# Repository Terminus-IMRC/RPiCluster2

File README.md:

# RPiCluster2

Yet another Raspberry Pi cluster, which can **chain up to 1+32 Raspberry
Pi's**!!!

The Pi on the Motherboard (master) is always turned on, while the other Pi's
(slaves) are turned on/off by the master via I2C.  The master can choose a slave
to communicate with over UART.

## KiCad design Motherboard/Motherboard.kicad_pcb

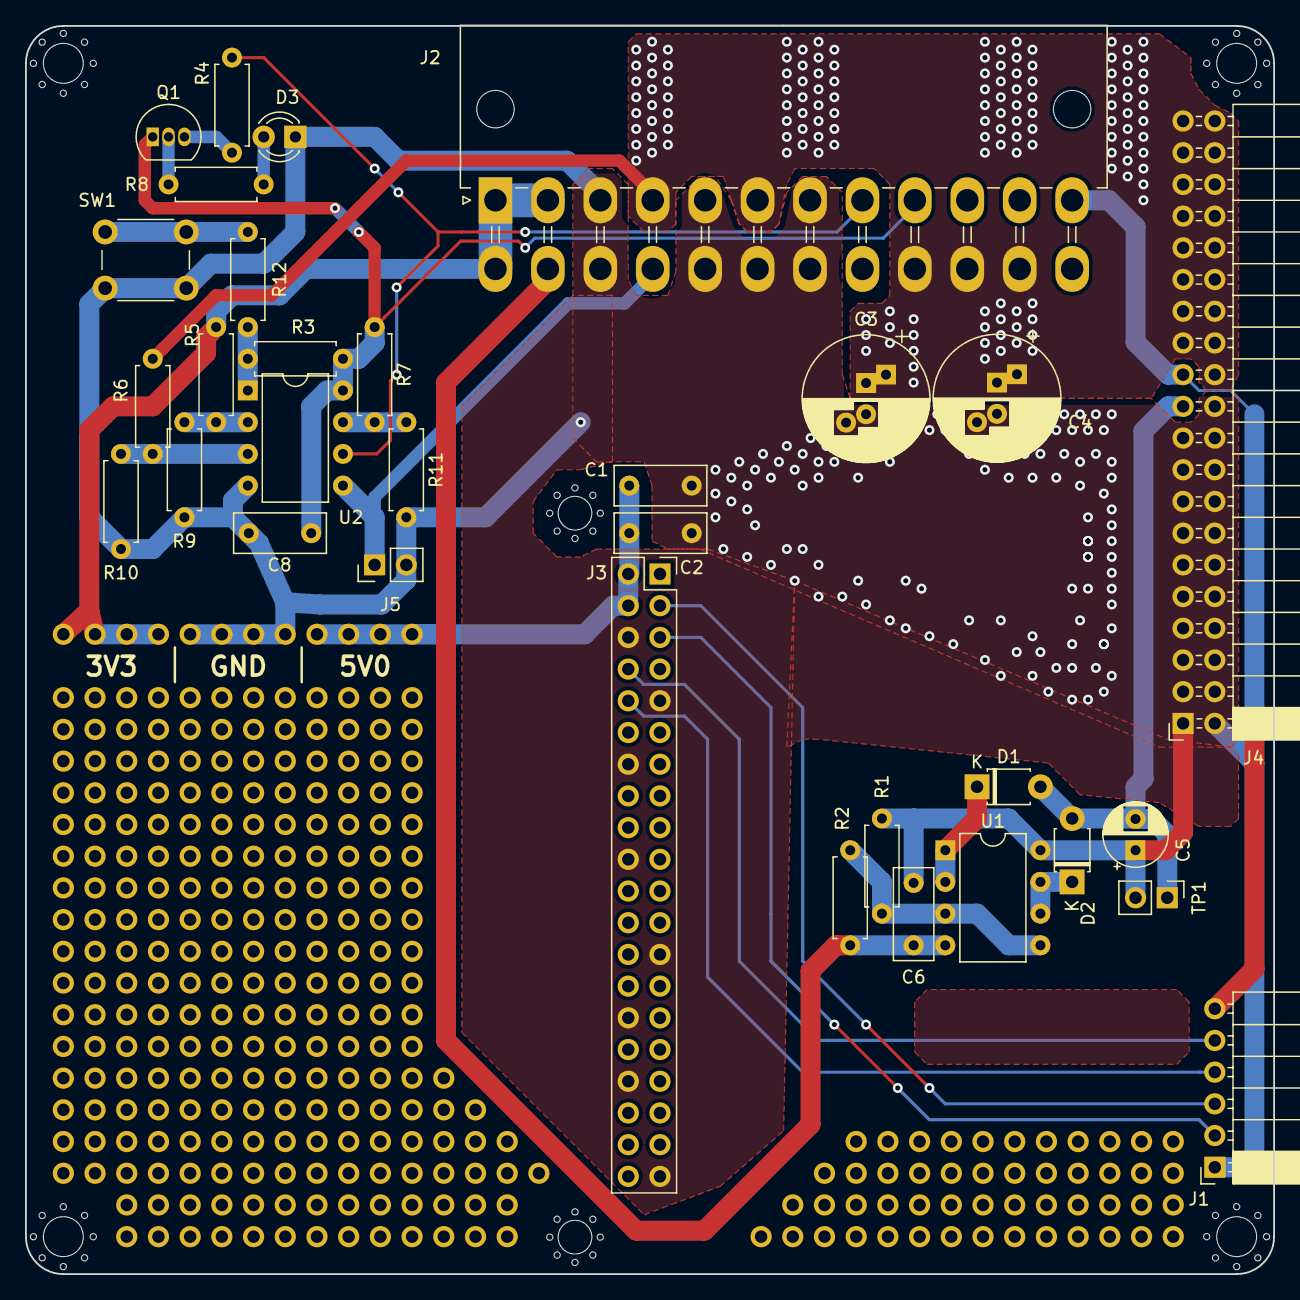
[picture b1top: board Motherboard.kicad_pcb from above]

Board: 2 copper layers, 100.0 x 100.0 mm, 32 parts (0 on the bottom side), 23 nets.

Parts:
C1, C2, C6, C8: 10u; C_Rect_L7.2mm_W3.0mm_P5.00mm_FKS2_FKP2_MKS2_MKP2
C3, C4: 470u; CP_Radial_D10.0mm_P2.50mm_P5.00mm
C5: 10u; CP_Radial_D5.0mm_P2.50mm
D1, D2: 0V5; D_T-1_P5.08mm_Horizontal
D3: LED_power_down; LED_D3.0mm
J1: Signal_socket; PinSocket_1x06_P2.54mm_Horizontal
J2: ATX_power; Molex_Mini-Fit_Jr_5569-24A2_2x12_P4.20mm_Horizontal
J3: RPi_server; PinSocket_2x20_P2.54mm_Vertical
J4: Power_socket; PinSocket_2x20_P2.54mm_Horizontal
J5: Test_~PS_ON~; PinHeader_1x02_P2.54mm_Vertical
Q1: 2SA1015; TO-92_Inline
R1: 2k; R_Axial_DIN0207_L6.3mm_D2.5mm_P7.62mm_Horizontal
R2, R8, R12: 10k; R_Axial_DIN0207_L6.3mm_D2.5mm_P7.62mm_Horizontal
R3: 47k; R_Axial_DIN0207_L6.3mm_D2.5mm_P7.62mm_Horizontal
R4: 1k; R_Axial_DIN0207_L6.3mm_D2.5mm_P7.62mm_Horizontal
R5: 6k8±5%; R_Axial_DIN0207_L6.3mm_D2.5mm_P7.62mm_Horizontal
R6, R7: 3k3±5%; R_Axial_DIN0207_L6.3mm_D2.5mm_P7.62mm_Horizontal
R9, R10, R11: 10k±1%; R_Axial_DIN0207_L6.3mm_D2.5mm_P7.62mm_Horizontal
SW1: Reset; SW_PUSH_6mm
TP1: Test_VEE; PinHeader_1x02_P2.54mm_Vertical
U1: LM358; DIP-8_W7.62mm
U2: ATtiny13A-PU; DIP-8_W7.62mm

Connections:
+3V3: J1.6, J2.1, J2.2, J2.12, J2.13, J4.23, R5.1
+5V: C1.2, C2.2, C3.1, C4.1, J2.4, J2.6, J2.21, J2.22, J2.23, J3.2, J3.4, J4.24, J4.25, J4.26, J4.27, J4.28, J4.29, J4.30, J4.31, J4.32, J4.33, J4.34, J4.35, J4.36, J4.37, J4.38, J4.39, J4.40, R6.1
+5VD: C8.2, J2.9, Q1.1, R3.1, R7.1, U2.8
-12V: C6.1, J2.14, R2.2, U1.4
/PWR_OK: J2.8, R4.2, U2.6
/RXD: J1.4, J3.10
/SCL: J1.2, J3.5
/SDA: J1.3, J3.3
/TXD: J1.5, J3.8
/~PS_ON~: J2.16, J5.1, U2.5
GND: C1.1, C2.1, C3.2, C4.2, C5.1, C6.2, C8.1, D3.1, J1.1, J2.3, J2.5, J2.7, J2.15, J2.17, J2.18, J2.19, J2.24, J3.6, J3.9, J3.14, J3.20, J3.25, J3.30, J3.34, J3.39, J4.1, J4.2, J4.3, J4.4, J4.5, J4.6, J4.7, J4.8, J4.9, J4.10, J4.11, J4.12, J4.13, J4.14, J4.15, J4.16, J4.17, J4.18, J4.19, J4.20, J4.22, J5.2, R1.1, R9.2, R10.2, R11.2, SW1.2, TP1.2, U1.8, U2.4
unnamed: D1.1, U1.1, U1.2
unnamed: D2.1, U1.6, U1.7
unnamed: D3.2, R8.2
unnamed: Q1.2, R8.1
unnamed: Q1.3, R4.1
unnamed: R1.2, R2.1, U1.3, U1.5
unnamed: R5.2, R9.1, U2.2
unnamed: R6.2, R10.1, U2.3
unnamed: R7.2, R11.1, U2.7
unnamed: R3.2, R12.1, U2.1
unnamed: R12.2, SW1.1
VEE: C5.2, D1.2, D2.2, J4.21, TP1.1

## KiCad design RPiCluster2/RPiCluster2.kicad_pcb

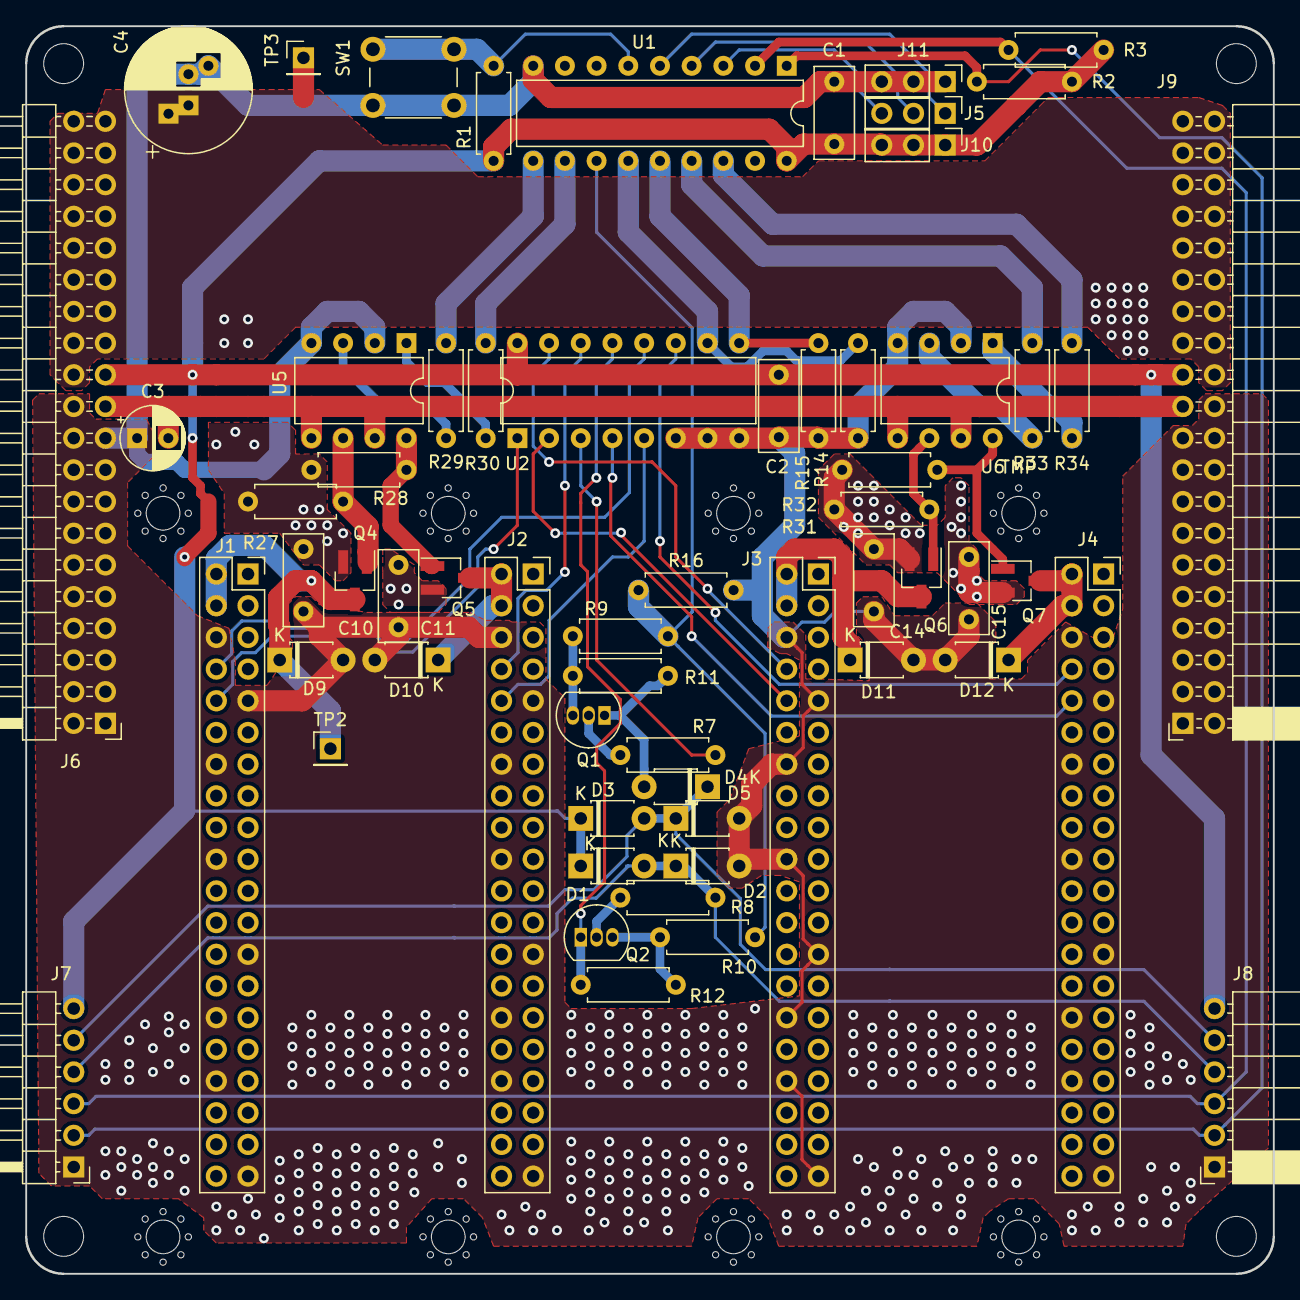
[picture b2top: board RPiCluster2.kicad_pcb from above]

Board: 2 copper layers, 100.0 x 100.0 mm, 62 parts (0 on the bottom side), 46 nets.

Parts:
C1, C2, C10, C11, C14, C15: 10u; C_Rect_L7.2mm_W3.0mm_P5.00mm_FKS2_FKP2_MKS2_MKP2
C3: 10u; CP_Radial_D5.0mm_P2.50mm
C4: 470u; CP_Radial_D10.0mm_P2.50mm_P5.00mm
D1, D2, D3, D4, D5: 0V5; D_T-1_P5.08mm_Horizontal
D9, D10, D11, D12: 1V0; D_T-1_P5.08mm_Horizontal
J1: RPi_slave_1; PinSocket_2x20_P2.54mm_Vertical
J2: RPi_slave_2; PinSocket_2x20_P2.54mm_Vertical
J3: RPi_slave_3; PinSocket_2x20_P2.54mm_Vertical
J4: RPi_slave_4; PinSocket_2x20_P2.54mm_Vertical
J5: Addr; PinHeader_1x03_P2.54mm_Vertical
J6: Power_header; PinHeader_2x20_P2.54mm_Horizontal
J7: Signal_header; PinHeader_1x06_P2.54mm_Horizontal
J8: Signal_socket; PinSocket_1x06_P2.54mm_Horizontal
J9: Power_socket; PinSocket_2x20_P2.54mm_Horizontal
J10: Addr_1; PinHeader_1x03_P2.54mm_Vertical
J11: Addr_0; PinHeader_1x03_P2.54mm_Vertical
Q1, Q2: 2SC1815; TO-92_Inline
Q4, Q5, Q6, Q7: IRLML6402; SOT-23_Handsoldering
R1, R14, R15, R16: 47k; R_Axial_DIN0207_L6.3mm_D2.5mm_P7.62mm_Horizontal
R2, R3, R11, R12, R27, R28, R31, R32: 10k; R_Axial_DIN0207_L6.3mm_D2.5mm_P7.62mm_Horizontal
R7, R8, R9, R10, R29, R30, R33, R34: 1k; R_Axial_DIN0207_L6.3mm_D2.5mm_P7.62mm_Horizontal
SW1: Reset; SW_PUSH_6mm
TMP: MountingHole_2.7mm_M2.5
TP2: Test_5V_SLV1; PinHeader_1x01_P2.54mm_Vertical
TP3: Test_5V; PinHeader_1x01_P2.54mm_Vertical
U1: MCP23008; DIP-18_W7.62mm
U2: 4052; DIP-16_W7.62mm
U5, U6: TLP627-2; DIP-8_W7.62mm

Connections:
5V_SLV1: D9.1, J1.2, J1.4, Q4.3, TP2.1
5V_SLV2: D10.1, J2.2, J2.4, Q5.3
5V_SLV3: D11.1, J3.2, J3.4, Q6.3
5V_SLV4: D12.1, J4.2, J4.4, Q7.3
+3V3: C1.2, C2.2, D1.1, D3.1, J6.23, J7.6, J8.6, J9.23, J10.1, J10.2, J10.3, R1.1, R2.1, R3.1, U1.18, U2.16
+5V: C4.1, C10.1, C11.1, C14.1, C15.1, J6.24, J6.25, J6.26, J6.27, J6.28, J6.29, J6.30, J6.31, J6.32, J6.33, J6.34, J6.35, J6.36, J6.37, J6.38, J6.39, J6.40, J9.24, J9.25, J9.26, J9.27, J9.28, J9.29, J9.30, J9.31, J9.32, J9.33, J9.34, J9.35, J9.36, J9.37, J9.38, J9.39, J9.40, Q4.2, Q5.2, Q6.2, Q7.2, R27.1, R28.1, R31.1, R32.1, TP3.1
/MUX_A: R14.1, U1.13, U2.10
/MUX_B: R15.1, U1.14, U2.9
/RXD1: J1.10, U2.1
/RXD2: J2.10, U2.5
/RXD3: J3.10, U2.2
/RXD4: J4.10, U2.4
/RXD_SLV: R7.1, U2.3
/SER_EN: R9.1, R10.1, R16.1, U1.12
/TXD1: J1.8, U2.12
/TXD2: J2.8, U2.14
/TXD3: J3.8, U2.15
/TXD4: J4.8, U2.11
/TXD_SLV: Q2.1, R12.2, U2.13
GND: C1.1, C2.1, C3.1, C4.2, C10.2, C11.2, C14.2, C15.2, D2.2, D5.2, D9.2, D10.2, D11.2, D12.2, J1.6, J1.9, J1.14, J1.20, J1.25, J1.30, J1.34, J1.39, J2.6, J2.9, J2.14, J2.20, J2.25, J2.30, J2.34, J2.39, J3.6, J3.9, J3.14, J3.20, J3.25, J3.30, J3.34, J3.39, J4.6, J4.9, J4.14, J4.20, J4.25, J4.30, J4.34, J4.39, J6.1, J6.2, J6.3, J6.4, J6.5, J6.6, J6.7, J6.8, J6.9, J6.10, J6.11, J6.12, J6.13, J6.14, J6.15, J6.16, J6.17, J6.18, J6.19, J6.20, J6.22, J7.1, J8.1, J9.1, J9.2, J9.3, J9.4, J9.5, J9.6, J9.7, J9.8, J9.9, J9.10, J9.11, J9.12, J9.13, J9.14, J9.15, J9.16, J9.17, J9.18, J9.19, J9.20, J9.22, J11.1, J11.2, J11.3, R14.2, R15.2, R16.2, SW1.2, U1.9, U2.6, U2.7, U2.8, U5.2, U5.4, U6.2, U6.4
unnamed: D4.2, Q1.1, R11.2
unnamed: J5.1, U1.5
unnamed: J5.2, U1.4
unnamed: J5.3, U1.3
unnamed: Q1.2, R7.2
unnamed: Q1.3, R9.2, R11.1
unnamed: Q2.2, R8.2
unnamed: Q2.3, R10.2, R12.1
unnamed: Q4.1, R27.2, U5.6
unnamed: Q5.1, R28.2, U5.8
unnamed: Q6.1, R31.2, U6.6
unnamed: Q7.1, R32.2, U6.8
unnamed: R1.2, SW1.1, U1.6
unnamed: R29.2, U5.3
unnamed: R30.2, U5.1
unnamed: R33.2, U6.3
unnamed: R34.2, U6.1
RXD: D1.2, D2.1, J7.4, J8.4, R8.1
SCL: J7.2, J8.2, R2.2, U1.1
SDA: J7.3, J8.3, R3.2, U1.2
SLV1: R29.1, U1.10
SLV2: R30.1, U1.11
SLV3: R33.1, U1.15
SLV4: R34.1, U1.16
TXD: D3.2, D4.1, D5.1, J7.5, J8.5
VEE: C3.2, J6.21, J9.21, U5.5, U5.7, U6.5, U6.7

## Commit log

2018-08-14 kicad: Add a legacy Microchip library
2018-08-14 RPiCluster2: Add WIP files
2018-08-15 RPiCluster2: Changes on power lines
2018-08-15 RPiCluster2: Pin order changes due to pcb layout limitations
2018-08-15 RPiCluster2: Reduce testing pins
2018-08-16 RPiCluster2: Add a WIP pcbnew file
2018-08-16 RPiCluster2: Update
2018-08-16 RPiCluster2: Pass DRC
2018-08-16 RPiCluster2: Bump to v0.0.0
2018-08-16 Motherboard: Add WIP schematics
2018-08-16 Add Motherboard project
2018-08-16 Motherboard: Add WIP PCB layout
2018-08-16 Motherboard: Update
2018-08-16 Add README.md
2018-08-16 README.md: Update
2018-08-17 Add .gitignore
2018-08-17 Add .editorconfig
2018-08-17 Motherboard: Use extensions for garber
2018-08-17 Add BackCover2 project
2018-08-17 BackCover2: Add schematics
2018-08-17 BackCover2: Add pcb layout
2018-08-17 BackCover2: Update
2018-08-17 rpicluster.py: Cluster controlling script (WIP)
2018-08-17 avr/simple: A simplified power supply controlling program
2018-08-17 avr/simple: Add Makefile
2018-08-17 avr/simple: Add .gitignore
2018-08-30 RPiCluster2: Fix ambiguous references
2018-08-30 RPiCluster2: Remove obsolete comment
2018-08-30 RPiCluster2: Avoid SER_EN from floating so that the board can be tested without MCP23008
2018-08-30 RPiCluster2: Fix swapping slave {TXD,RXD} lines
2018-08-30 Motherboard: Also monitor the PS_OK line
2018-08-30 avr/simple: Fix the baud rate for lower AVR clock
2018-08-30 avr/simple: Also monitor the PS_OK line
2018-08-30 avr/simple: Wait for a sufficient time for power supply to turn on
2018-08-30 avr/simple: Use float for clock value
2018-08-30 avr/simple: Add -std=c99 to the compile option
2018-09-03 rpicluster.py: Fix to import ceil directly from math
2018-09-09 rpicluster2.py: Moved to scripts/ directory
2018-09-10 scripts/rpicluster.py: Add an option to check power status
2018-09-10 scripts/rpicluster.py: Report as powered-off for slave which does not exist
2018-09-10 scripts/rpicluster.py: Say error if corresponding RPiCluster2 is not found when selecting serial
2018-09-10 scripts/rpicluster.py: Specify -1 to disable serial
2018-09-10 scripts/rpicluster.py: Add an option to check serial status
2018-09-10 scripts/rpicluster.py: Print power status as integer
2018-09-10 scripts/rpicluster.sh: RPiCluster2 configuration dialog
2018-09-10 scripts/rpicluster.sh: Eliminate obsolete debug codes
2018-09-10 scripts/rpicluster.sh: Speed-up power status checking
2018-09-10 scripts/rpicluster.sh: Change the order of the main menu

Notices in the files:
Motherboard/Motherboard.kicad_pcb:
© 2018 Sugizaki Yukimasa
RPiCluster2/RPiCluster2.kicad_pcb:
(c) 2018 Sugizaki Yukimasa
